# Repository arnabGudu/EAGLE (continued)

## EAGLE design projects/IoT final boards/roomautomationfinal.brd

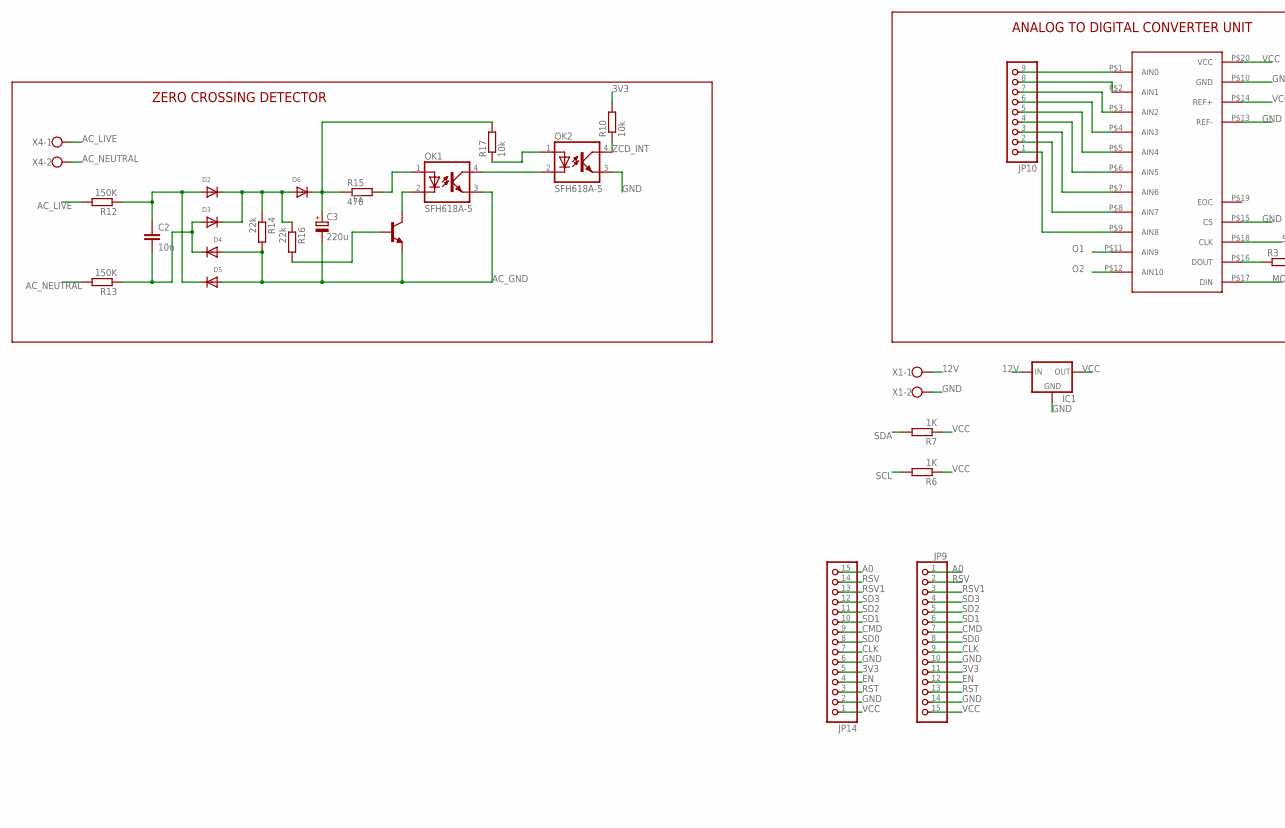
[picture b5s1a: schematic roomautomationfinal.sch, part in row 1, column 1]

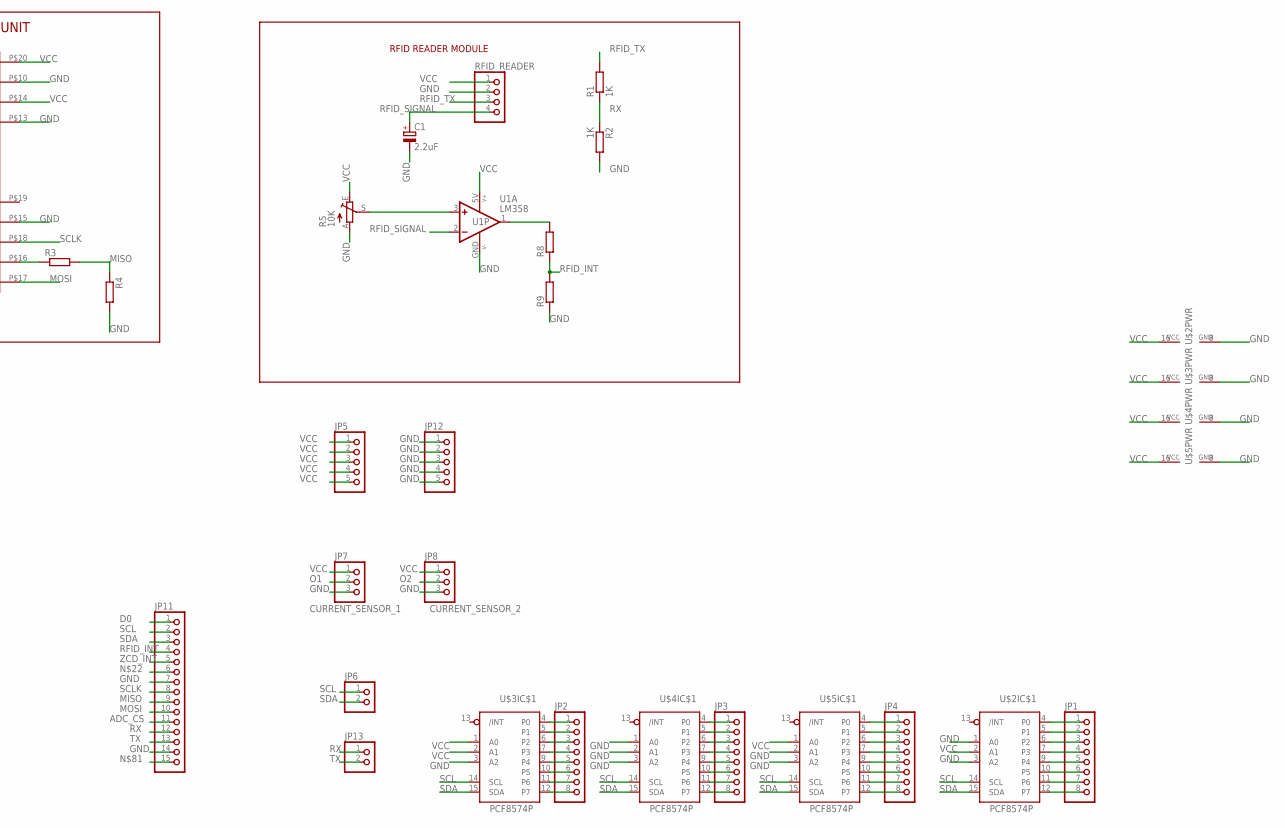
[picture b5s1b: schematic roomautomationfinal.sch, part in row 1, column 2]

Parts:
C1: 2.2uF; E2,5-5
C2: 10n; C150-054X183
C3: 220u; E5-10,5
D2, D3, D4, D5, D6: DIODEDO-1N4148; DO-1N4148
IC1: 78MXXS
JP1, JP2, JP3, JP4: HEADER-1X8; 1X08_OVAL
JP5, JP12: PINHD-1X5; 1X05
JP6, JP13: PINHD-1X2; 1X02
JP7, JP8: PINHD-1X3; 1X03
JP9, JP11, JP14: PINHD-1X15; 1X15
JP10: PINHD-1X9; 1X09
OK1: SFH618A-5; DIP4
OK2: SFH618A-5; DIP4; MPN SFH618A-5
R1, R2, R6, R7: 1K; 0207/10
R3, R4, R8, R9: R-EU_0207/10; 0207/10
R5: 10K; B25P
R10: 10k; 0207/10
R12, R13: 150K; 0207/10
R14, R16: 22k; 0207/10
R15: 470; 0617V
R17: 10k; 0617V
RFID_READER: HEADER-1X4; 1X04_OVAL
T1: -NPN-TO92-CBE; TO92-CBE
U1: LM358; DIL08
U$2, U$3, U$4, U$5: PCF8574P; DIL16
U$6: TLC2543
X1: W237-102
X4: W237-102; MPN 237-102

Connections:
3V3: JP9.11, JP14.5, R10.2
12V: IC1.IN, X1.1
A0: JP9.1, JP14.15
AC_GND: C3.-, D4.A, D5.A, OK1.3 (EMIT), R14.2, T1.E
AC_LIVE: R12.2, X4.1
AC_NEUTRAL: R13.2, X4.2
ADC_CS: JP11.11
CLK: JP9.9, JP14.7
CMD: JP9.7, JP14.9
D0: JP11.1
EN: JP9.12, JP14.4
GND: C1.-, IC1.GND, JP7.3, JP8.3, JP9.10, JP9.14, JP11.7, JP11.14, JP12.1, JP12.2, JP12.3, JP12.4, JP12.5, JP14.2, JP14.6, OK2.3 (EMIT), R2.2, R4.2, R5.A, R9.1, RFID_READER.2, U1.GND (V-), U$2.1 (A0), U$2.3 (A2), U$2.8 (GND), U$3.3 (A2), U$3.8 (GND), U$4.1 (A0), U$4.2 (A1), U$4.3 (A2), U$4.8 (GND), U$5.2 (A1), U$5.3 (A2), U$5.8 (GND), U$6.P$10 (GND), U$6.P$13 (REF-), U$6.P$15 (CS), X1.2
MISO: JP11.9, R3.2, R4.1
MOSI: JP11.10, U$6.P$17 (DIN)
unnamed: R3.1, U$6.P$16 (DOUT)
unnamed: JP10.9, U$6.P$1 (AIN0)
unnamed: JP10.8, U$6.P$2 (AIN1)
unnamed: JP10.7, U$6.P$3 (AIN2)
unnamed: JP10.6, U$6.P$4 (AIN3)
unnamed: JP10.5, U$6.P$5 (AIN4)
unnamed: JP10.4, U$6.P$6 (AIN5)
unnamed: JP10.3, U$6.P$7 (AIN6)
unnamed: JP10.2, U$6.P$8 (AIN7)
unnamed: JP10.1, U$6.P$9 (AIN8)
unnamed: C2.1, D2.A, D5.C, R12.1
unnamed: C2.2, D3.A, D4.C, R13.1
unnamed: R5.S, U1.3 (+IN)
unnamed: D2.C, D3.C, D6.A, R14.1, R16.1
unnamed: R8.2, U1.1 (OUT)
unnamed: JP1.1, U$2.4 (P0)
unnamed: JP1.2, U$2.5 (P1)
unnamed: JP1.3, U$2.6 (P2)
unnamed: C3.+, D6.C, R15.1, R17.2
unnamed: JP1.4, U$2.7 (P3)
unnamed: JP1.5, U$2.9 (P4)
unnamed: JP1.6, U$2.10 (P5)
unnamed: R16.2, T1.B
unnamed: JP1.7, U$2.11 (P6)
unnamed: JP1.8, U$2.12 (P7)
unnamed: JP2.1, U$3.4 (P0)
unnamed: JP2.2, U$3.5 (P1)
unnamed: JP2.3, U$3.6 (P2)
unnamed: JP2.4, U$3.7 (P3)
unnamed: JP2.5, U$3.9 (P4)
unnamed: JP2.6, U$3.10 (P5)
unnamed: JP2.7, U$3.11 (P6)
unnamed: JP2.8, U$3.12 (P7)
unnamed: JP3.1, U$4.4 (P0)
unnamed: JP3.2, U$4.5 (P1)
unnamed: JP3.3, U$4.6 (P2)
unnamed: JP3.4, U$4.7 (P3)
unnamed: JP3.5, U$4.9 (P4)
unnamed: JP3.6, U$4.10 (P5)
unnamed: JP3.7, U$4.11 (P6)
unnamed: JP3.8, U$4.12 (P7)
unnamed: JP4.1, U$5.4 (P0)
unnamed: JP4.2, U$5.5 (P1)
unnamed: JP4.3, U$5.6 (P2)
unnamed: JP4.4, U$5.7 (P3)
unnamed: JP4.5, U$5.9 (P4)
unnamed: JP4.6, U$5.10 (P5)
unnamed: JP4.7, U$5.11 (P6)
unnamed: JP4.8, U$5.12 (P7)
unnamed: OK2.1 (A), R17.1
unnamed: OK1.4 (COL), OK2.2 (C)
unnamed: OK1.1 (A), R15.2
unnamed: OK1.2 (C), T1.C
O1: JP7.2, U$6.P$11 (AIN9)
O2: JP8.2, U$6.P$12 (AIN10)
RFID_INT: JP11.4, R8.1, R9.2
RFID_SIGNAL: C1.+, RFID_READER.4, U1.2 (-IN)
RFID_TX: R1.2, RFID_READER.3
RST: JP9.13, JP14.3
RSV: JP9.2, JP14.14
RSV1: JP9.3, JP14.13
RX: JP11.12, JP13.1, R1.1, R2.1
SCL: JP6.1, JP11.2, R6.2, U$2.14 (SCL), U$3.14 (SCL), U$4.14 (SCL), U$5.14 (SCL)
SCLK: JP11.8, U$6.P$18 (CLK)
SD0: JP9.8, JP14.8
SD1: JP9.6, JP14.10
SD2: JP9.5, JP14.11
SD3: JP9.4, JP14.12
SDA: JP6.2, JP11.3, R7.2, U$2.15 (SDA), U$3.15 (SDA), U$4.15 (SDA), U$5.15 (SDA)
TX: JP11.13, JP13.2
VCC: IC1.OUT, JP5.1, JP5.2, JP5.3, JP5.4, JP5.5, JP7.1, JP8.1, JP9.15, JP14.1, R5.E, R6.1, R7.1, RFID_READER.1, U1.5V (V+), U$2.2 (A1), U$2.16 (VCC), U$3.1 (A0), U$3.2 (A1), U$3.16 (VCC), U$4.16 (VCC), U$5.1 (A0), U$5.16 (VCC), U$6.P$14 (REF+), U$6.P$20 (VCC)
ZCD_INT: JP11.5, OK2.4 (COL), R10.1

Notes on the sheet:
ANALOG TO DIGITAL CONVERTER UNIT
RFID READER MODULE
ZERO CROSSING DETECTOR
CURRENT_SENSOR_1
CURRENT_SENSOR_2

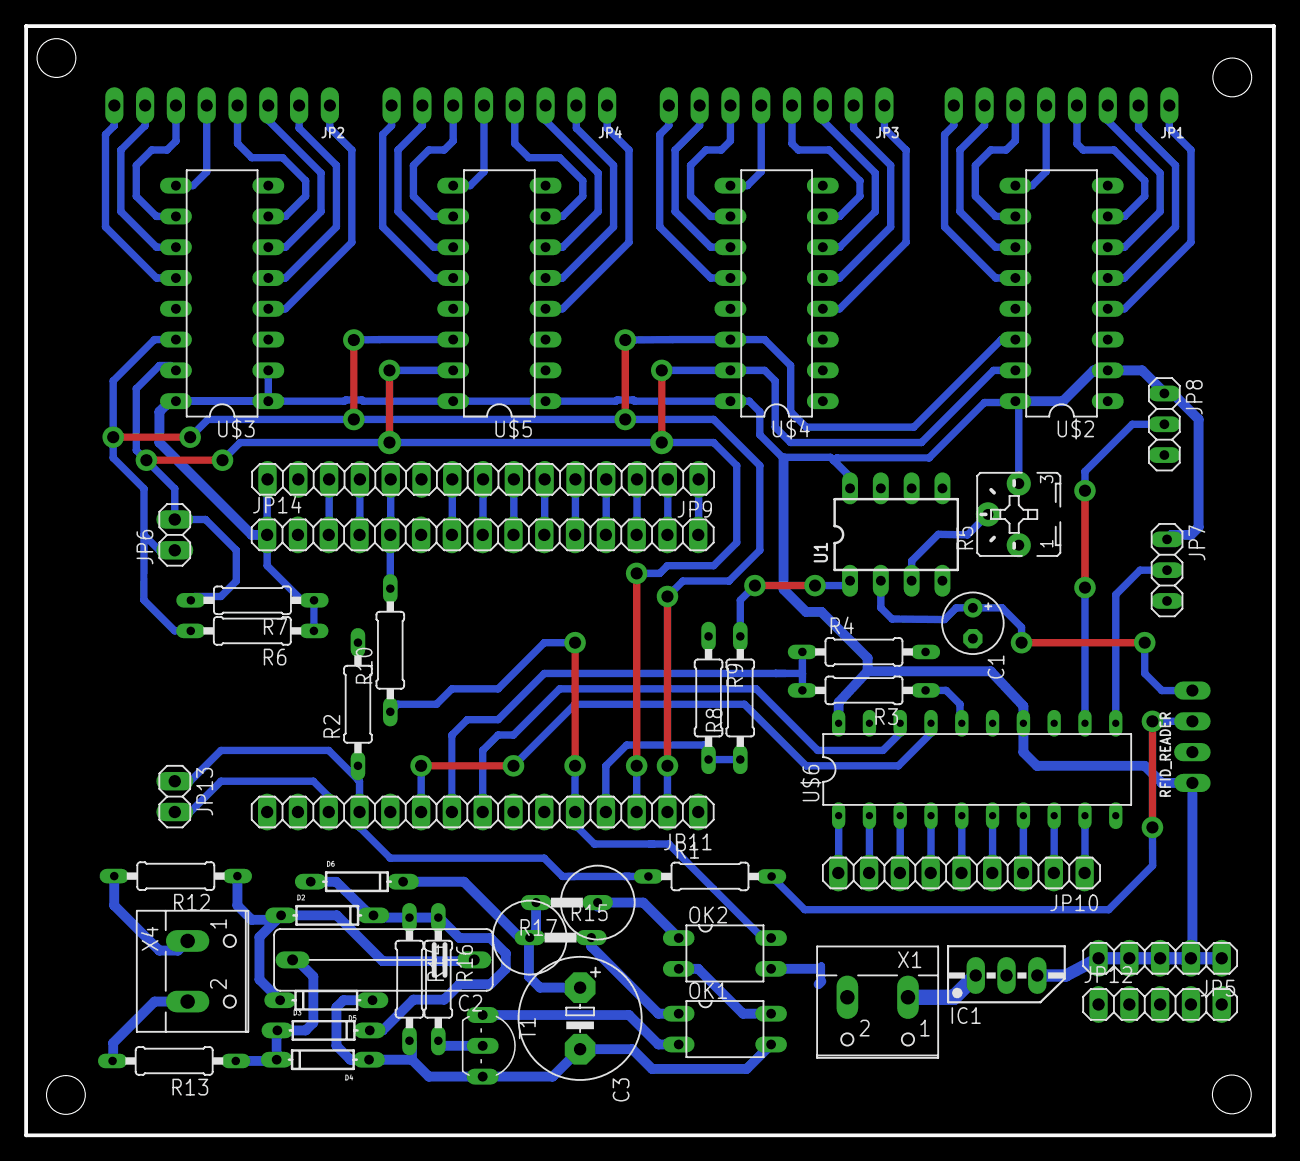
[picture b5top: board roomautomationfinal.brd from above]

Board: 2 copper layers, 102.9 x 91.5 mm, 51 parts (0 on the bottom side), 84 nets.

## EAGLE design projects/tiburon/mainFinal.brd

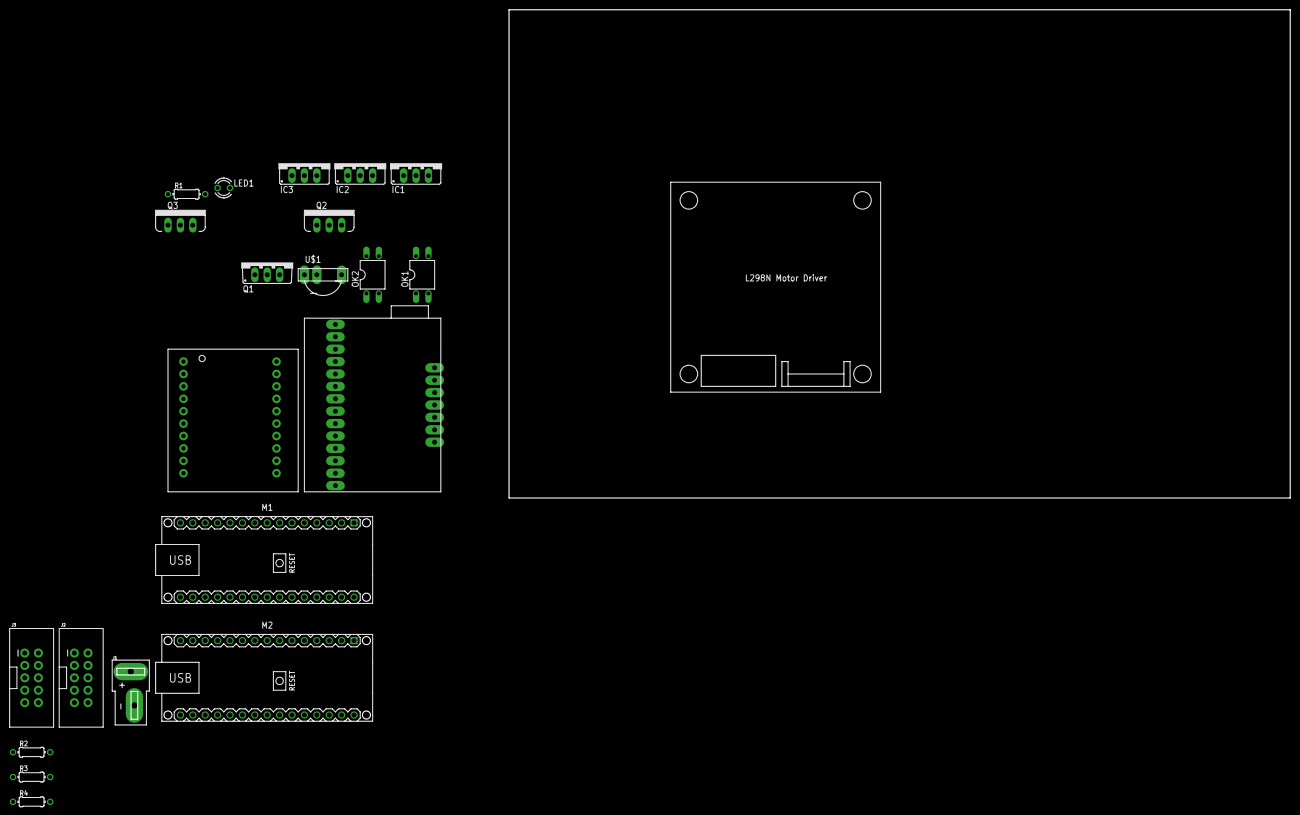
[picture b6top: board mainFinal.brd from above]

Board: 2 copper layers, 22 parts (0 on the bottom side), 8 nets, no tracks yet.

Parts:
IC1, IC2, IC3: 78XXS
J1: DEANS
J2, J3: 2X5-SHROUDED_LOCK
LED1: LED3MM
M1, M2: ARDUINO-NANO-3.0
OK1, OK2: TIL191; DIL04
Q1: IRF512; TO220BV
Q2, Q3: MOSFET-PCHANNELFQP27P06; TO220V
R1, R2, R3, R4: 0204/7
U$1: TSOP34X; TSOP3XXX
U$2: DIGITAL_ISOLATOR; DIGITAL_ISOLATOR_MODULE
U$3: SERVO_CONTROLLER
U$4: L298N

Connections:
3V3: M1.J2.14, M2.J2.14
5V: M1.J2.4, M2.J2.4
GND.1: M1.J1.4, M2.J1.4
GND.2: M1.J2.2, M2.J2.2
unnamed: OK1.4, Q2.1, R4.1
unnamed: Q2.2, R4.2
unnamed: OK1.3, Q2.3
VIN: M1.J2.1, M2.J2.1

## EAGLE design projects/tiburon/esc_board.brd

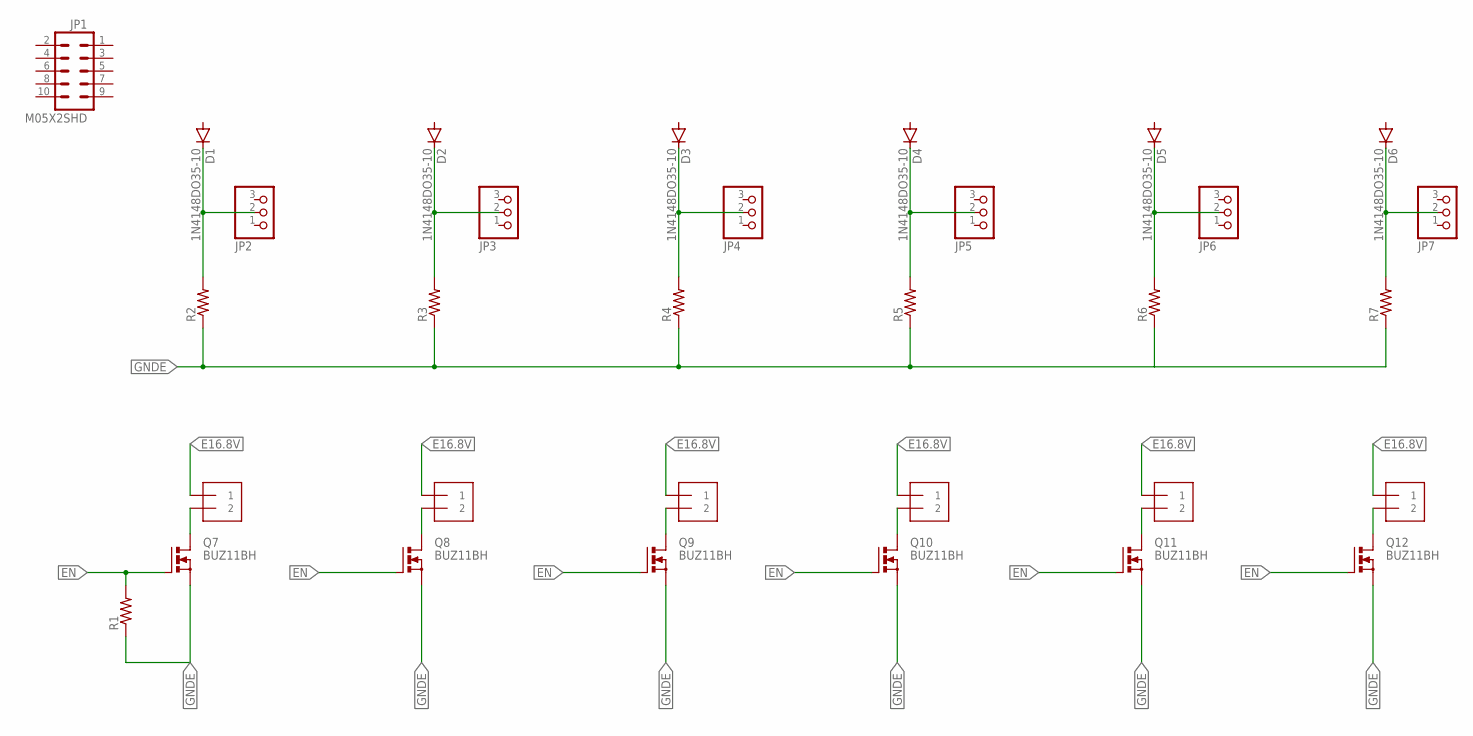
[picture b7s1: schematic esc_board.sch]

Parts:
D1, D2, D3, D4, D5, D6: 1N4148DO35-10; DO35-10
J7, J8, J9, J10, J11, J12: 1X2-3.5MM
JP1: M05X2SHD; 2X5-SHROUDED
JP2, JP3, JP4, JP5, JP6, JP7: PINHD-1X3; 1X03
Q7, Q8, Q9, Q10, Q11, Q12: BUZ11BH; TO220BH
R1, R2, R3, R4, R5, R6, R7: R-US_0204/7; 0204/7

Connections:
E16.8V: J7.1, J8.1, J9.1, J10.1, J11.1, J12.1
EN: Q7.G, Q8.G, Q9.G, Q10.G, Q11.G, Q12.G, R1.2
GNDE: Q7.S, Q8.S, Q9.S, Q10.S, Q11.S, Q12.S, R1.1, R2.1, R3.1, R4.1, R5.1, R6.1, R7.1
unnamed: J7.2, Q7.D
unnamed: D1.C, JP2.2, R2.2
unnamed: J8.2, Q8.D
unnamed: D2.C, JP3.2, R3.2
unnamed: J9.2, Q9.D
unnamed: D3.C, JP4.2, R4.2
unnamed: J10.2, Q10.D
unnamed: D4.C, JP5.2, R5.2
unnamed: J11.2, Q11.D
unnamed: D5.C, JP6.2, R6.2
unnamed: D6.C, JP7.2, R7.2
unnamed: J12.2, Q12.D

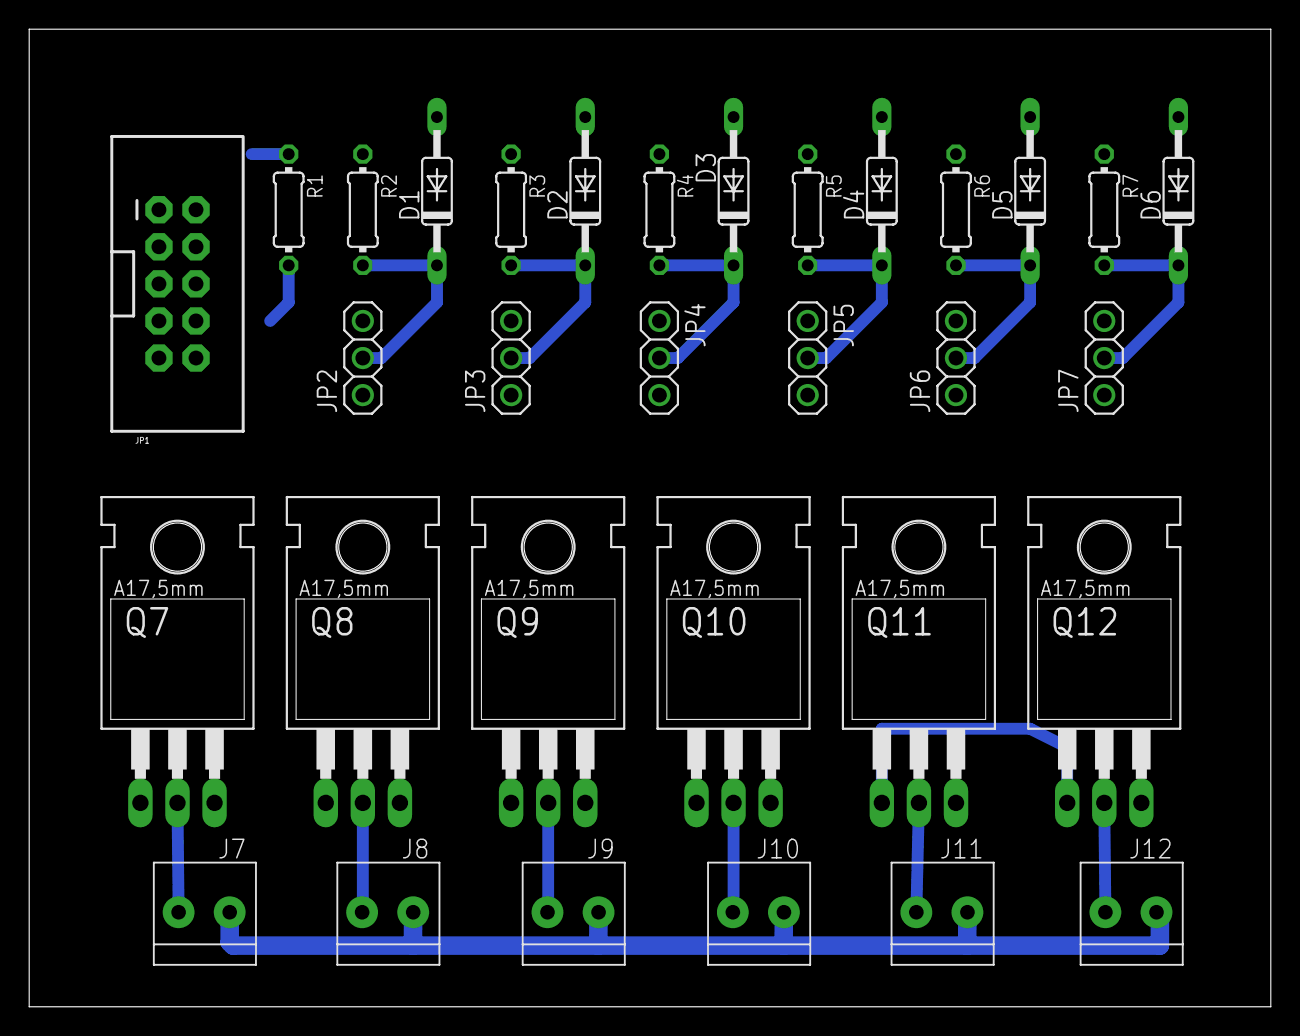
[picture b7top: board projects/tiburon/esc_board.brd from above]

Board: 2 copper layers, 85.1 x 67.0 mm, 32 parts (0 on the bottom side), 15 nets.

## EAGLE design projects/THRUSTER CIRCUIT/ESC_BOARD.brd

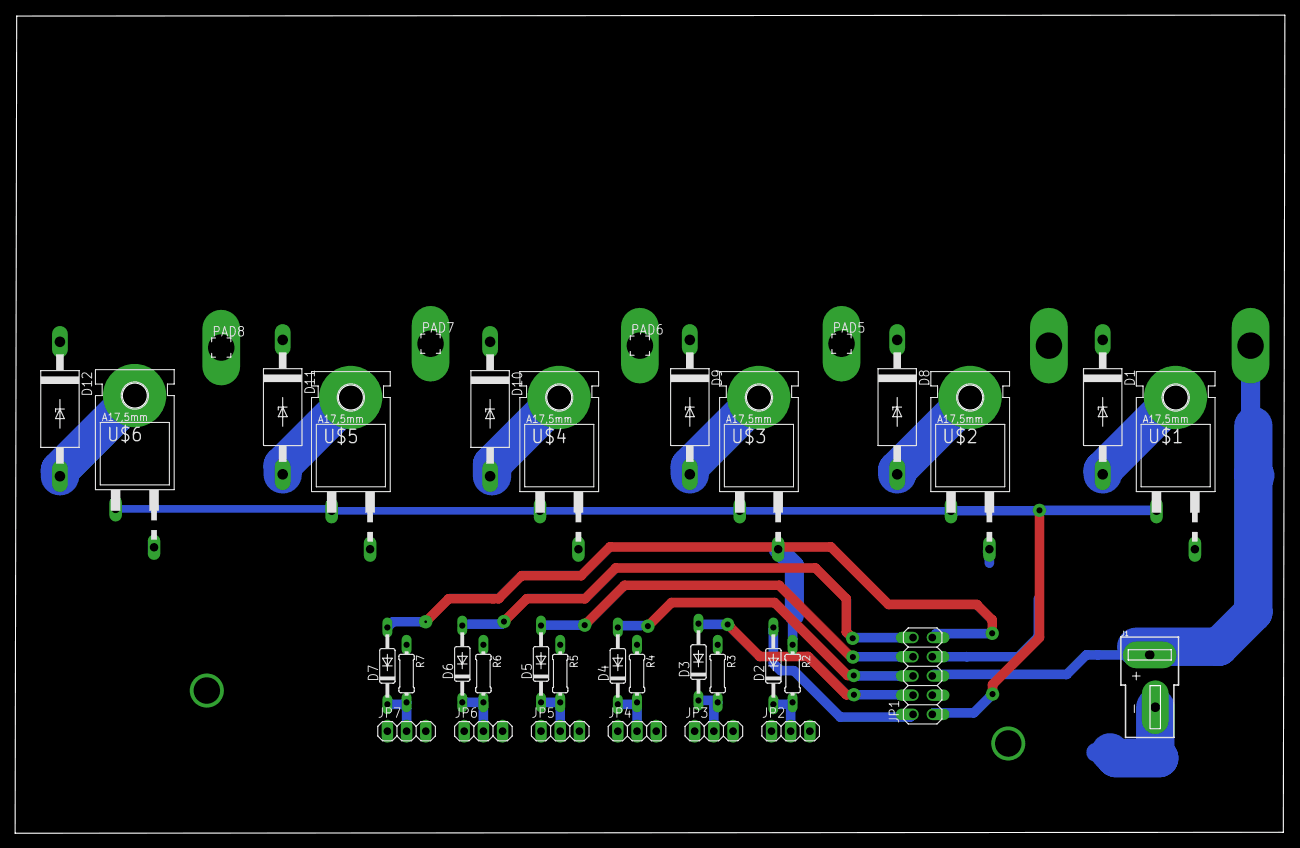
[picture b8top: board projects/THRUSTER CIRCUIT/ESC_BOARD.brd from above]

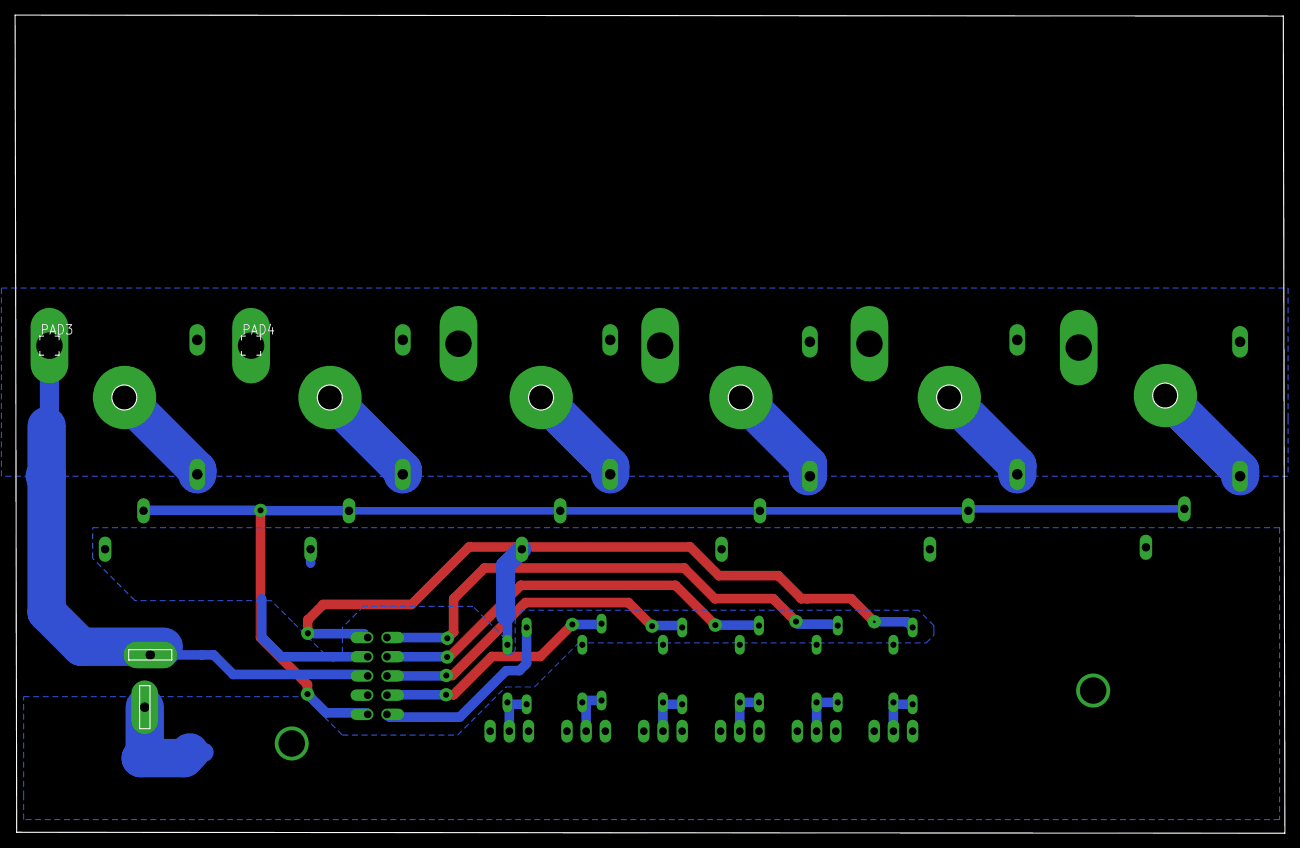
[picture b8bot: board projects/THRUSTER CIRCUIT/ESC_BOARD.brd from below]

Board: 2 copper layers, 167.9 x 108.2 mm, 38 parts (2 on the bottom side), 21 nets.

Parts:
D1, D8, D9, D10, D11, D12: CB429-17
D2, D3, D4, D5, D6, D7: 1N4446; DO35-10
J1: DEANS
JP1: 2X05
JP2, JP3, JP4, JP5, JP6, JP7: 1X03
PAD3, PAD4, PAD5, PAD6, PAD7, PAD8: 2,54/1,1
R2, R3, R4, R5, R6, R7: 10K; 0204/7
U$1, U$2, U$3, U$4, U$5, U$6: TO220; IRF540

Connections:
ESC_1: D1.A, U$1.2
ESC_1_SIGNAL: D2.A, JP1.2
ESC_2: D8.A, U$2.2
ESC_2_SIGNAL: D3.A, JP1.4
ESC_3: D9.A, U$3.2
ESC_3_SIGNAL: D4.A, JP1.6
ESC_4: D10.A, U$4.2
ESC_4_SIGNAL: D5.A, JP1.8
ESC_5: D11.A, U$5.2
ESC_5_SIGNAL: D6.A, JP1.10
ESC_6: D12.A, U$6.2
ESC_6_SIGNAL: D7.A, JP1.9
ESC_BATTERY_MAIN: D1.C, D8.C, D9.C, D10.C, D11.C, D12.C, J1.+, JP1.5, PAD3.1, PAD4.1, PAD5.1, PAD6.1, PAD7.1, PAD8.1
ESC_GND: J1.-, JP1.7, R2.1, R3.1, R4.1, R5.1, R6.1, R7.1, U$1.3, U$2.3, U$3.3, U$4.3, U$5.3, U$6.3
SIGNAL_1: D2.C, JP2.2, R2.2
SIGNAL_2: D3.C, JP3.2, R3.2
SIGNAL_3: D4.C, JP4.2, R4.2
SIGNAL_4: D5.C, JP5.2, R5.2
SIGNAL_5: D6.C, JP6.2, R6.2
SIGNAL_6: D7.C, JP7.2, R7.2
THRUSTER_ENABLE_ESC: JP1.1, U$1.1, U$2.1, U$3.1, U$4.1, U$5.1, U$6.1

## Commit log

2019-11-08 added
